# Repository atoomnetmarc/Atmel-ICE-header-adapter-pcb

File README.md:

Atmel-ICE with header adapter

Consult the [Internet Archive](https://web.archive.org/web/20190417234006/https://atoomnet.net/atmel-ice-header-adapter/) for a historic snapshot of the original page describing the use.

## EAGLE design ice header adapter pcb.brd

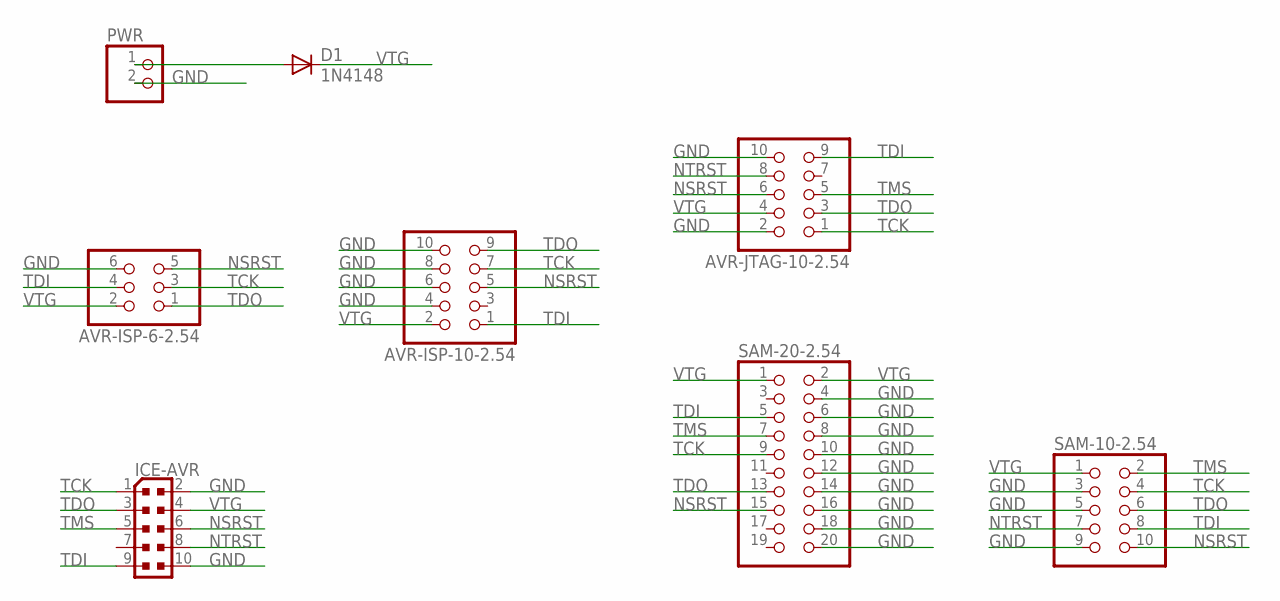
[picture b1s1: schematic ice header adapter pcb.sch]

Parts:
AVR-ISP-6-2.54: PINHD-2X3; 2X03
AVR-ISP-10-2.54: PINHD-2X5; 2X05
AVR-JTAG-10-2.54: PINHD-2X5; 2X05
D1: 1N4148; DO35-7
ICE-AVR: PINHEAD_PINHD-2X5PASSO127; PINHEAD_2X05_127
PWR: PINHD-1X2/90; 1X02/90
SAM-10-2.54: PINHD-2X5; 2X05
SAM-20-2.54: PINHD-2X10; 2X10

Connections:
GND: AVR-ISP-6-2.54.6, AVR-ISP-10-2.54.4, AVR-ISP-10-2.54.6, AVR-ISP-10-2.54.8, AVR-ISP-10-2.54.10, AVR-JTAG-10-2.54.2, AVR-JTAG-10-2.54.10, ICE-AVR.2, ICE-AVR.10, PWR.2, SAM-10-2.54.3, SAM-10-2.54.5, SAM-10-2.54.9, SAM-20-2.54.4, SAM-20-2.54.6, SAM-20-2.54.8, SAM-20-2.54.10, SAM-20-2.54.12, SAM-20-2.54.14, SAM-20-2.54.16, SAM-20-2.54.18, SAM-20-2.54.20
unnamed: D1.A, PWR.1
NSRST: AVR-ISP-6-2.54.5, AVR-ISP-10-2.54.5, AVR-JTAG-10-2.54.6, ICE-AVR.6, SAM-10-2.54.10, SAM-20-2.54.15
NTRST: AVR-JTAG-10-2.54.8, ICE-AVR.8, SAM-10-2.54.7
TCK: AVR-ISP-6-2.54.3, AVR-ISP-10-2.54.7, AVR-JTAG-10-2.54.1, ICE-AVR.1, SAM-10-2.54.4, SAM-20-2.54.9
TDI: AVR-ISP-6-2.54.4, AVR-ISP-10-2.54.1, AVR-JTAG-10-2.54.9, ICE-AVR.9, SAM-10-2.54.8, SAM-20-2.54.5
TDO: AVR-ISP-6-2.54.1, AVR-ISP-10-2.54.9, AVR-JTAG-10-2.54.3, ICE-AVR.3, SAM-10-2.54.6, SAM-20-2.54.13
TMS: AVR-JTAG-10-2.54.5, ICE-AVR.5, SAM-10-2.54.2, SAM-20-2.54.7
VTG: AVR-ISP-6-2.54.2, AVR-ISP-10-2.54.2, AVR-JTAG-10-2.54.4, D1.C, ICE-AVR.4, SAM-10-2.54.1, SAM-20-2.54.1, SAM-20-2.54.2

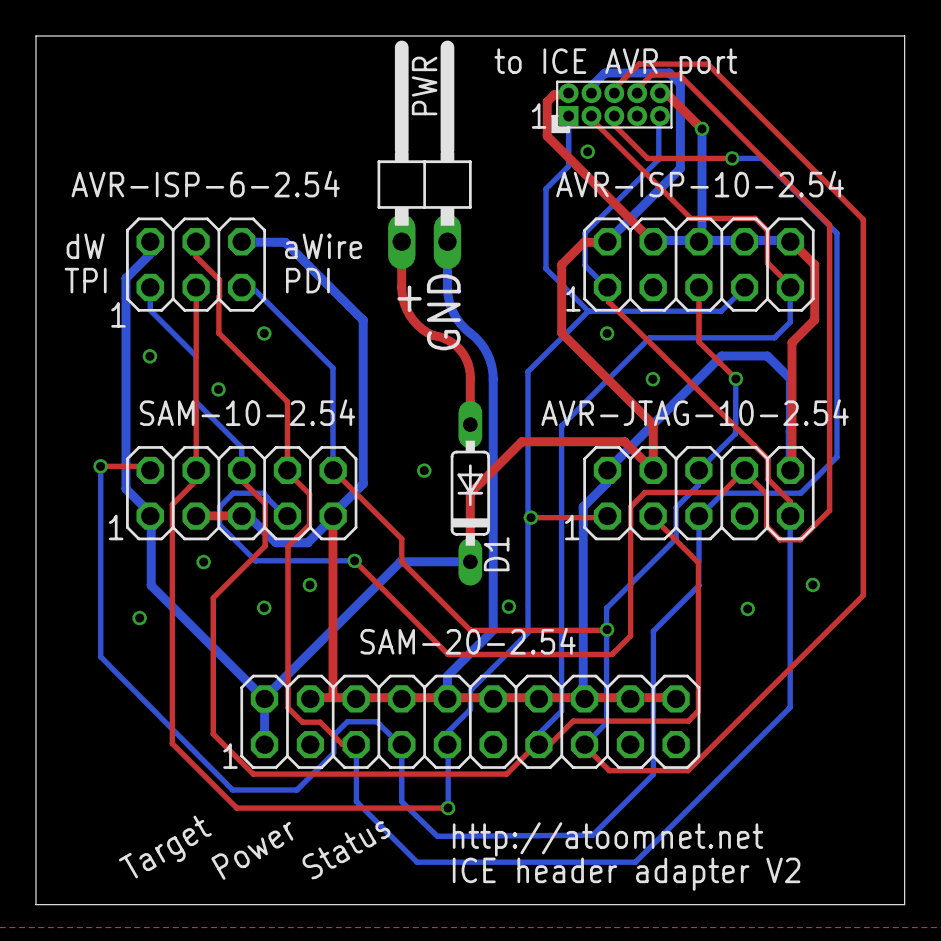
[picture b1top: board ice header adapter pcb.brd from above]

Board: 2 copper layers, 48.3 x 48.3 mm, 8 parts (0 on the bottom side), 9 nets.

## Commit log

2021-09-11 Added v2 adapter

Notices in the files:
README.md:
License: Apache 2.0
